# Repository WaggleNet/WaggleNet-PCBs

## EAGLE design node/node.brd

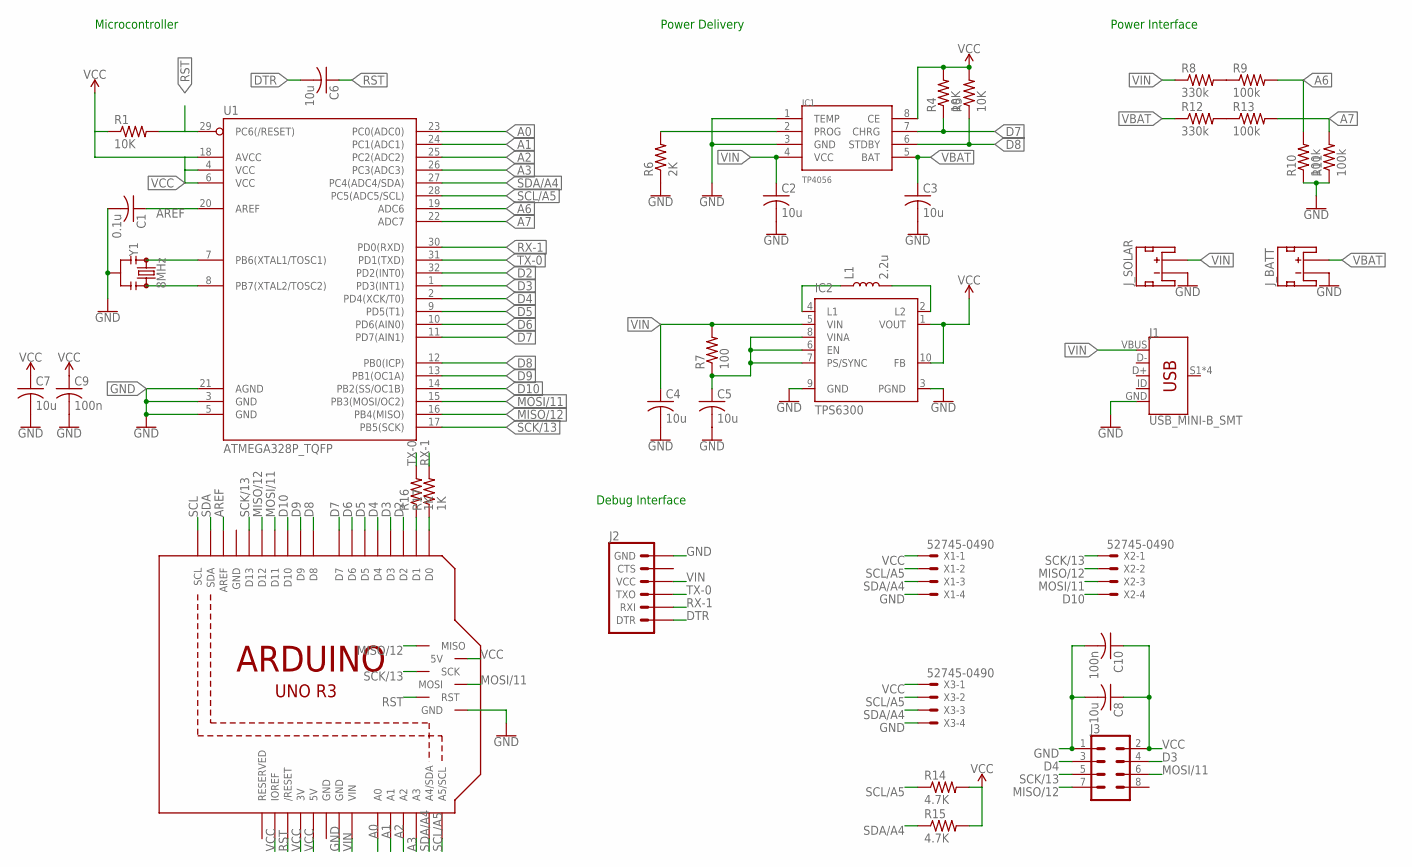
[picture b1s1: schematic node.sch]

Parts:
C1: 0.1u; C0805; MPN CC0603KRX7R7BB104
C2, C3, C4, C5, C6, C7, C8: 10u; C0805; MPN 08056D106KAT2A
C9, C10: 100n; C0805; MPN 08056D106KAT2A
IC1: TP4056; SOP-8
IC2: TPS6300; DRC-S-PVSON-N10; MPN TPS63001DRCT
J1: USB_MINI-B_SMT; USB-MINIB; MPN 67503-1020
J2: 6_PIN_SERIAL_TARGETSILK; 6_PIN_SERIAL_TARGET_SIDE_W_SILK
J3: CONN_04X2; 2X4
J_BATT: JST_2MM_MALE; JST-2-SMD; MPN S2B-PH-SM4-TB(LF)(SN)
J_SOLAR: JST_2MM_MALE; JST-2-SMD; MPN S2B-PH-SM4-TB(LF)(SN)
L1: 2.2u; 0805; MPN MLF2012A2R2K
M1: ARDUINO_R3_ICSP; ARDUINOR3_ICSP
R1, R4, R5: 10K; R0805
R6: 2K; R0805; MPN CR0805-JW-222ELF
R7: 100; R0805; MPN RC0805FR-07100RL
R8, R12: 330k; R0805; MPN MC01W08051330K
R9, R10, R11, R13: 100k; R0805; MPN CRCW0805100KFKEA
R14, R15: 4.7K; R0805; MPN RC0805JR-074K7L
R16, R17: 1K; R0805; MPN MC0805S8F1001T5E
U1: ATMEGA328P_TQFP; TQFP32-08; MPN ATMEGA328P-AU
X1, X2, X3: 52745-0490; MPN 52745-0497.
Y1: 8MHz; RESONATOR-SMD-3.2X1.3; MPN PBRC8.00HR50X000

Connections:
A0: M1.A0, U1.23 (PC0(ADC0))
A1: M1.A1, U1.24 (PC1(ADC1))
A2: M1.A2, U1.25 (PC2(ADC2))
A3: M1.A3, U1.26 (PC3(ADC3))
A6: R9.2, R10.2, U1.19 (ADC6)
A7: R11.2, R13.2, U1.22 (ADC7)
AREF: C1.1, M1.AREF, U1.20 (AREF)
D2: M1.D2, U1.32 (PD2(INT0))
D3: J3.4, M1.D3, U1.1 (PD3(INT1))
D4: J3.3, M1.D4, U1.2 (PD4(XCK/T0))
D5: M1.D5, U1.9 (PD5(T1))
D6: M1.D6, U1.10 (PD6(AIN0))
D7: IC1.7 (CHRG), M1.D7, R4.1, U1.11 (PD7(AIN1))
D8: IC1.6 (STDBY), M1.D8, R5.1, U1.12 (PB0(ICP))
D9: M1.D9, U1.13 (PB1(OC1A))
D10: M1.D10, U1.14 (PB2(SS/OC1B)), X2.4
DTR: C6.2, J2.P$1 (DTR)
GND: C1.2, C2.2, C3.2, C4.2, C5.2, C7.2, C8.2, C9.2, C10.2, IC1.1 (TEMP), IC1.3 (GND), IC2.3 (PGND), IC2.9 (GND), J1.GND, J2.P$6 (GND), J3.1, J_BATT.1 (-), J_SOLAR.1 (-), M1.GND, M1.GND@1 (GND), M1.GND@2 (GND), M1.GND@3 (GND), R6.1, R10.1, R11.1, U1.3 (GND), U1.5 (GND), U1.21 (AGND), X1.4, X3.4, Y1.2
MISO/12: J3.7, M1.D12, M1.MISO, U1.16 (PB4(MISO)), X2.2
MOSI/11: J3.6, M1.D11, M1.MOSI, U1.15 (PB3(MOSI/OC2)), X2.3
unnamed: U1.8 (PB7(XTAL2/TOSC2)), Y1.3
unnamed: U1.7 (PB6(XTAL1/TOSC1)), Y1.1
unnamed: M1.D0, R17.1
unnamed: IC2.2 (L2), L1.2
unnamed: IC2.4 (L1), L1.1
unnamed: IC1.2 (PROG), R6.2
unnamed: R8.2, R9.1
unnamed: R12.2, R13.1
unnamed: M1.D1, R16.1
RST: C6.1, M1.RESET (/RESET), M1.RESET_ICSP (RST), R1.2, U1.29 (PC6(/RESET))
RX-1: J2.P$3 (RXI), R17.2, U1.30 (PD0(RXD))
SCK/13: J3.5, M1.D13, M1.SCK, U1.17 (PB5(SCK)), X2.1
SCL: M1.SCL
SCL/A5: M1.A5 (A5/SCL), R14.1, U1.28 (PC5(ADC5/SCL)), X1.2, X3.2
SDA: M1.SDA
SDA/A4: M1.A4 (A4/SDA), R15.1, U1.27 (PC4(ADC4/SDA)), X1.3, X3.3
TX-0: J2.P$2 (TXO), R16.2, U1.31 (PD1(TXD))
VBAT: C3.1, IC1.5 (BAT), J_BATT.2 (+), R12.1
VCC: C7.1, C8.1, C9.1, C10.1, IC1.8 (CE), IC2.1 (VOUT), IC2.10 (FB), J3.2, M1.3V, M1.5V, M1.5V_ICSP (5V), M1.IOREF, R1.1, R4.2, R5.2, R14.2, R15.2, U1.4 (VCC), U1.6 (VCC), U1.18 (AVCC), X1.1, X3.1
VIN: C2.1, C4.1, IC1.4 (VCC), IC2.5 (VIN), J1.VBUS, J2.P$4 (VCC), J_SOLAR.2 (+), M1.VIN, R7.2, R8.1
VINA: C5.1, IC2.6 (EN), IC2.7 (PS/SYNC), IC2.8 (VINA), R7.1

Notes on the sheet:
Microcontroller
Power Delivery
Power Interface
Debug Interface

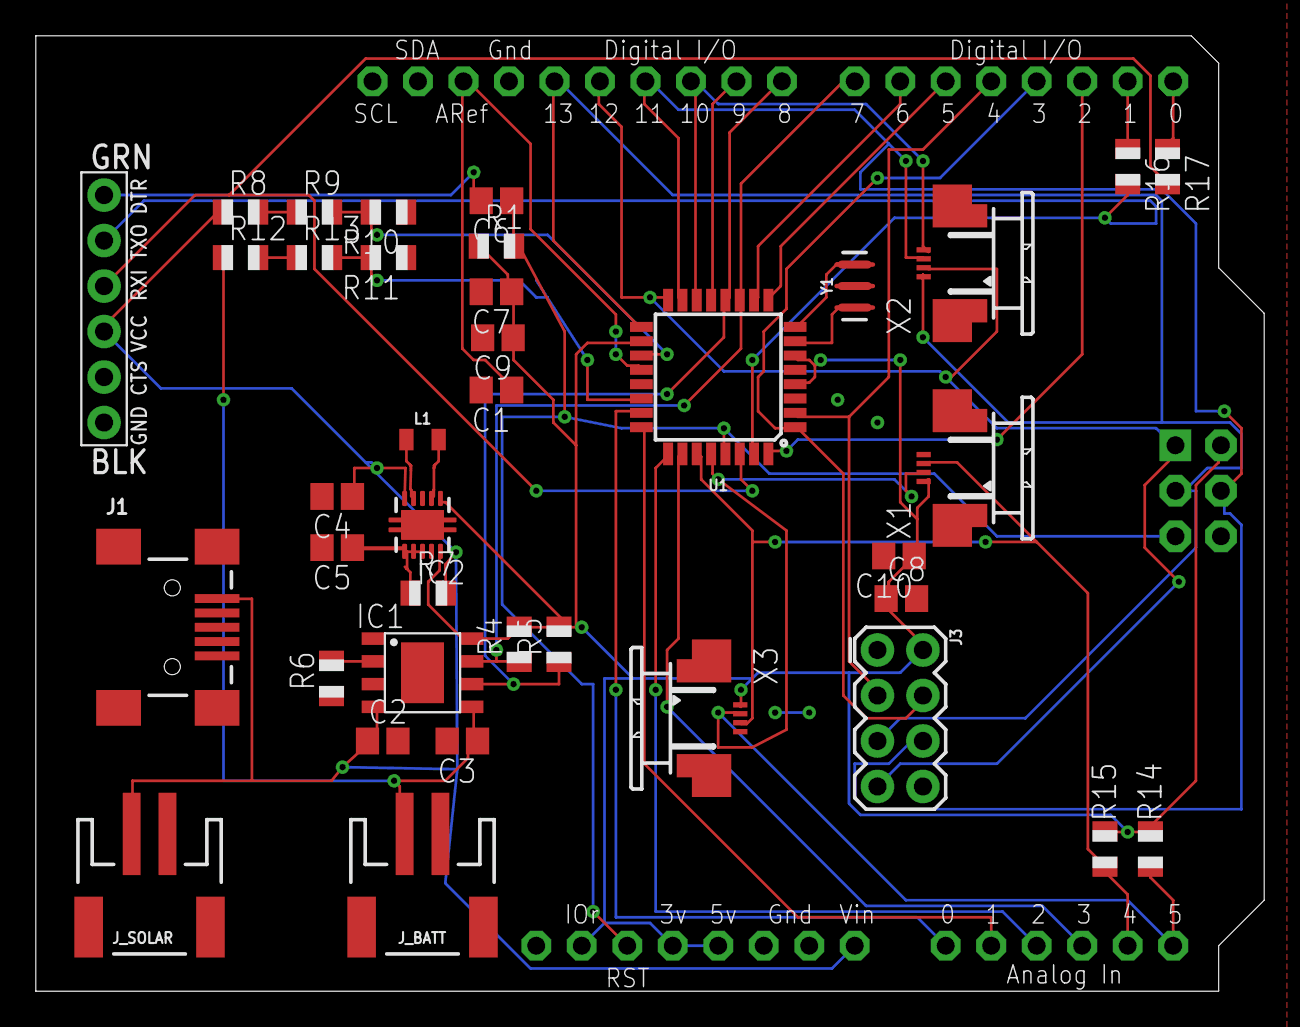
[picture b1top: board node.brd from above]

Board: 2 copper layers, 68.6 x 53.3 mm, 39 parts (0 on the bottom side), 39 nets.

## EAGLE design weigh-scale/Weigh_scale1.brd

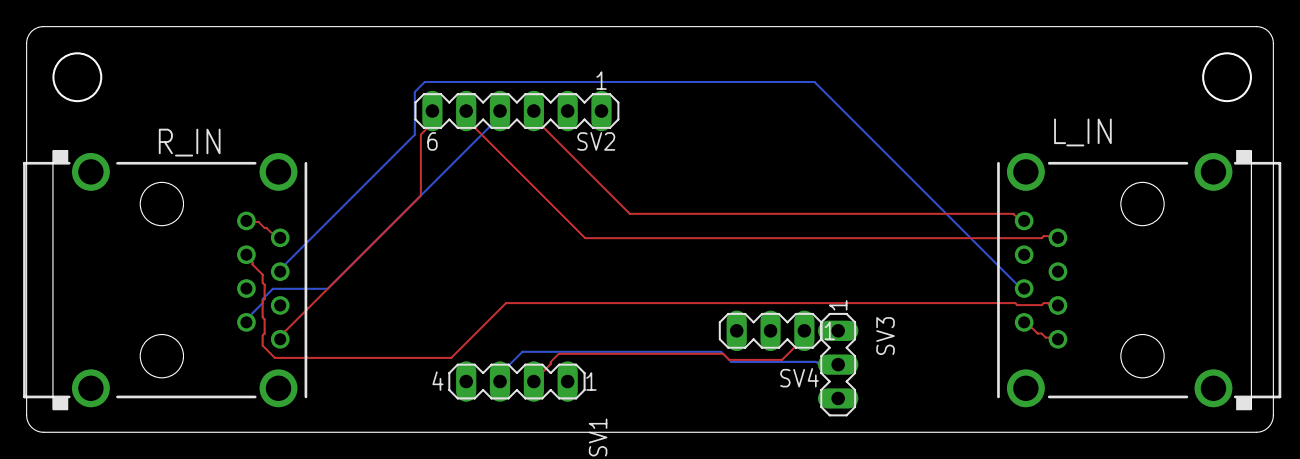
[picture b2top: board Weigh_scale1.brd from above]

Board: 2 copper layers, 93.6 x 30.5 mm, 6 parts (0 on the bottom side), 12 nets.

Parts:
L_IN: flip; RJ45-SHIELD2
R_IN: flip; RJ45-SHIELD2
SV1: MA04-1
SV2: MA06-1
SV3, SV4: MA03-1

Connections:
A+: L_IN.8, SV2.3
A-: R_IN.7, SV2.4
E+: R_IN.8, SV2.6
E-: L_IN.7, SV2.5
GND: SV1.1, SV3.3
HX_DATA: SV1.2, SV4.1
HX_SCK_A2: SV1.3, SV3.2
unnamed: L_IN.1, L_IN.2
unnamed: R_IN.1, R_IN.2
unnamed: L_IN.3, R_IN.3
unnamed: L_IN.4, R_IN.4
VCC: SV1.4, SV3.1

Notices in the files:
parts and their libraries:
SparkFun-Connectors: Licensing: Creative Commons ShareAlike 4.0 International - https://creativecommons.org/licenses/by-sa/4.0
